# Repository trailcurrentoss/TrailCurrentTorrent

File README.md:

# TrailCurrent Torrent

CAN-controlled 8-channel PWM power distribution module for vehicle lighting and accessory control with OTA firmware update capability and mDNS self-discovery. Up to 3 Torrent modules can operate on the same CAN bus, each with a unique address and CAN IDs. Part of the [TrailCurrent](https://trailcurrent.com) open-source vehicle platform.

## Hardware Overview

- **Microcontroller:** ESP32 (WROOM32)
- **Function:** 8-channel PWM lighting/accessory controller with CAN bus interface
- **Key Features:**
  - 8 independent MOSFET-driven PWM outputs (0-255 brightness)
  - CAN bus communication at 500 kbps
  - Up to 3 modules on the same bus via compile-time `TORRENT_ADDRESS` (0-2)
  - Individual and master on/off/brightness control
  - Animated light sequences (startup, interior, exterior)
  - Over-the-air (OTA) firmware updates via WiFi
  - mDNS self-discovery for automatic registration with Headwaters
  - WiFi credentials provisioned dynamically over CAN bus
  - Hierarchical PCB schematic design (5 sheets)

## Hardware Requirements

### Components

- **Microcontroller:** ESP32 development board
- **CAN Transceiver:** Vehicle CAN bus interface (TX: GPIO 15, RX: GPIO 13)
- **MOSFET Drivers:** 8 channels for PWM output switching
- **DIP Switches:** Configuration switches

### Pin Connections

**PWM Outputs:**

| GPIO | Function |
|------|----------|
| 32 | Output 1 |
| 33 | Output 2 |
| 26 | Output 3 |
| 14 | Output 4 |
| 4 | Output 5 |
| 17 | Output 6 |
| 19 | Output 7 |
| 23 | Output 8 |

### KiCAD Library Dependencies

This project uses the consolidated [TrailCurrentKiCADLibraries](https://github.com/trailcurrentoss/TrailCurrentKiCADLibraries).

**Setup:**

```bash
# Clone the library
git clone git@github.com:trailcurrentoss/TrailCurrentKiCADLibraries.git

# Set environment variables (add to ~/.bashrc or ~/.zshrc)
export TRAILCURRENT_SYMBOL_DIR="/path/to/TrailCurrentKiCADLibraries/symbols"
export TRAILCURRENT_FOOTPRINT_DIR="/path/to/TrailCurrentKiCADLibraries/footprints"
export TRAILCURRENT_3DMODEL_DIR="/path/to/TrailCurrentKiCADLibraries/3d_models"
```

See [KICAD_ENVIRONMENT_SETUP.md](https://github.com/trailcurrentoss/TrailCurrentKiCADLibraries/blob/main/docs/KICAD_ENVIRONMENT_SETUP.md) in the library repository for detailed setup instructions.

## Opening the Project

1. **Set up environment variables** (see Library Dependencies above)
2. **Open KiCAD:**
   ```bash
   kicad EDA/trailcurrent-torrent.kicad_pro
   ```
3. **Verify libraries load** - All symbol and footprint libraries should resolve without errors
4. **View 3D models** - Open PCB and press `Alt+3` to view the 3D visualization

### Schematic Sheets

The design uses a hierarchical schematic with dedicated sheets:
- **Root** - Top-level connections
- **Power** - Power distribution and regulation
- **CAN** - CAN bus transceiver interface
- **MCU** - ESP32 microcontroller and support circuits
- **MOSFETs** - 8-channel MOSFET driver outputs
- **DIP Switch** - Configuration switches

## Firmware

Built with [ESP-IDF](https://docs.espressif.com/projects/esp-idf/en/latest/esp32/) (Espressif IoT Development Framework) targeting the ESP32.

### Prerequisites

Install ESP-IDF v5.x following the [official guide](https://docs.espressif.com/projects/esp-idf/en/latest/esp32/get-started/).

### Build and Flash

```bash
# Set up ESP-IDF environment
source ~/esp/v5.5.2/esp-idf/export.sh

# First time: set chip target
idf.py set-target esp32

# Build firmware (default address 0)
idf.py build

# Build for a specific module address (0-2)
idf.py build -DTORRENT_ADDRESS=1

# Flash and monitor (serial)
idf.py -p /dev/ttyUSB0 flash monitor
```

### Multi-Instance Addressing

Up to 3 Torrent modules can share the same CAN bus. Each module is built with a unique address that determines its CAN IDs:

```bash
idf.py build                      # Address 0 (default)
idf.py build -DTORRENT_ADDRESS=1  # Address 1
idf.py build -DTORRENT_ADDRESS=2  # Address 2
```

Each address produces a firmware binary with unique CAN IDs (see CAN Bus Protocol below). Flash each binary to a different ESP32. At boot, the module logs its address and CAN IDs for verification.

#### Building All Variants

Use `build-all.sh` to build all 3 address variants in a single run:

```bash
./build-all.sh
```

This produces two binaries per address — one for OTA updates, one for the web flasher:

| File | Contents | Used By |
|------|----------|---------|
| `build/torrent_addr{N}.bin` | Application image only | Headwaters OTA (`deploy.sh`, `ota.js`), direct `curl` uploads |
| `build/torrent_addr{N}_merged.bin` | Bootloader + partition table + OTA data + application | Web flasher (full flash at 0x0) |

The two binary types exist because OTA and the web flasher write to different targets. Headwaters OTA sends the binary to the device's `/ota` HTTP endpoint, which calls `esp_ota_write` to write it to a single app partition. That function validates the image as an application — a merged binary starts with the bootloader instead of an app header, so it would fail validation. The web flasher writes the entire flash contents starting at offset 0x0, so it needs all partitions combined into one file.

#### Creating a GitHub Release

After building all variants, attach all 6 binaries (3 app-only + 3 merged) as release assets:

```bash
git tag -a v1.0.0 -m "Firmware release v1.0.0"
git push origin v1.0.0

gh release create v1.0.0 \
  build/torrent_addr0.bin \
  build/torrent_addr1.bin \
  build/torrent_addr2.bin \
  build/torrent_addr0_merged.bin \
  build/torrent_addr1_merged.bin \
  build/torrent_addr2_merged.bin \
  --repo trailcurrentoss/TrailCurrentTorrent \
  --title "v1.0.0" \
  --notes "Firmware release v1.0.0"
```

Both the Headwaters deployment system and the web flasher pull from GitHub releases. The web flasher matches `_merged.bin` files by name for full-flash use. The Headwaters deployment system (`fetch-firmware.sh`) downloads the app-only `torrent_addr{N}.bin` files for OTA delivery.

### OTA Firmware Update

After initial serial flash, firmware can be updated over WiFi:

1. **Provision WiFi credentials** via CAN bus (message ID 0x01)
2. **Trigger OTA mode** via CAN bus (message ID 0x00 with device MAC bytes)
3. **Upload firmware** via HTTP — always use the app-only binary (`torrent_addr{N}.bin`), never the merged binary:
   ```bash
   curl -X POST http://esp32-XXYYZZ.local/ota --data-binary @build/torrent_addr0.bin
   ```

The device enters OTA mode for 3 minutes, starts an HTTP server, and advertises via mDNS. After a successful upload it reboots into the new firmware. Dual OTA partitions provide rollback safety.

### mDNS Self-Discovery

Modules register themselves with the Headwaters controller:

1. **Provision WiFi credentials** via CAN bus (message ID 0x01)
2. **Send discovery trigger** via CAN bus (message ID 0x02, broadcast)
3. Module joins WiFi and advertises a `_trailcurrent._tcp` mDNS service with metadata:
   - `type=torrent` — module type
   - `addr=0` — module address (0-2, from `TORRENT_ADDRESS` build flag)
   - `canid=0x1B` — CAN status message ID (varies by address)
   - `fw=1.0.0` — firmware version
4. Headwaters confirms registration by calling `GET /discovery/confirm`
5. Module tears down WiFi and returns to normal CAN operation

Discovery can be triggered again on subsequent CAN 0x02 broadcasts. A module that is already running a discovery session ignores additional triggers until the current session completes or times out (3 minutes).

### Logging

Firmware uses the ESP-IDF logging system (`ESP_LOGI`, `ESP_LOGW`, `ESP_LOGE`). Log output is available on the serial monitor at 115200 baud.

Log verbosity can be configured at build time via `idf.py menuconfig` under **Component config > Log output**.

**WiFi Credentials:**
- WiFi credentials are provisioned dynamically via CAN bus (Message ID 0x01)
- Credentials are stored in NVS (non-volatile storage) and persist across reboots
- For standalone testing, credentials can be set manually via NVS

### CAN Bus Protocol

CAN IDs are computed as `BASE + TORRENT_ADDRESS`. The table below shows base IDs and per-instance values.

**Receive (Bus → Module):**

| Base ID | Addr 0 | Addr 1 | Addr 2 | Description |
|---------|--------|--------|--------|-------------|
| — | 0x00 | 0x00 | 0x00 | OTA update trigger (3 bytes: last 3 MAC bytes for device targeting) |
| — | 0x01 | 0x01 | 0x01 | WiFi credential provisioning (chunked SSID/password protocol) |
| — | 0x02 | 0x02 | 0x02 | Discovery trigger (broadcast, no payload) |
| — | 0x04 | 0x04 | 0x04 | Version report on boot: `[mac3, mac4, mac5, major, minor, patch]` |
| 0x15 | 0x15 | 0x16 | 0x17 | Set brightness (byte 0 = channel 0-7, byte 1 = PWM value 0-255) |
| 0x18 | 0x18 | 0x19 | 0x1A | Toggle channel on/off (byte 0 = channel 0-7, 8=all off/on, 9=all on) |
| 0x33 | 0x33 | 0x34 | 0x35 | Trigger light sequence (byte 0: 0=interior, 1=exterior) |

**Transmit (Module → Bus):**

| Base ID | Addr 0 | Addr 1 | Addr 2 | Interval | Description |
|---------|--------|--------|--------|----------|-------------|
| 0x1B | 0x1B | 0x1C | 0x1D | 33 ms (30 Hz) | Status report — current PWM values for all 8 channels (8 bytes) |

### WiFi Credential Provisioning Protocol

WiFi credentials are sent over CAN in chunks (max 6 payload bytes per CAN frame):

| Step | data[0] | Payload | Description |
|------|---------|---------|-------------|
| 1 | 0x01 | ssid_len, pass_len, ssid_chunks, pass_chunks | Start message |
| 2 | 0x02 | chunk_index, up to 6 bytes | SSID chunk |
| 3 | 0x03 | chunk_index, up to 6 bytes | Password chunk |
| 4 | 0x04 | XOR checksum | End/commit message |

All messages are sent on CAN ID 0x01. A 5-second timeout resets the state machine if the sequence is interrupted.

## Manufacturing

- **PCB Files:** Ready for fabrication via standard PCB services (JLCPCB, OSH Park, etc.)
- **BOM Generation:** Export BOM from KiCAD schematic (Tools > Generate BOM)
- **JLCPCB Assembly:** See [BOM_ASSEMBLY_WORKFLOW.md](https://github.com/trailcurrentoss/TrailCurrentKiCADLibraries/blob/main/tools/BOM_ASSEMBLY_WORKFLOW.md) for detailed assembly workflow

## Project Structure

```
├── EDA/                          # KiCAD hardware design files
│   ├── trailcurrent-torrent.kicad_pro
│   ├── trailcurrent-torrent.kicad_sch  # Root schematic
│   ├── can.kicad_sch             # CAN subsystem
│   ├── mcu.kicad_sch             # MCU subsystem
│   ├── power.kicad_sch           # Power subsystem
│   ├── mosfets.kicad_sch         # 8-channel MOSFET drivers
│   ├── dip_switch.kicad_sch      # Configuration switches
│   └── trailcurrent-torrent.kicad_pcb  # PCB layout
├── CAD/                          # FreeCAD case design and 3D models
│   ├── trailcurrent-torrent-case.FCStd
│   └── TrailCurrentTorrent.3mf
├── main/                         # ESP-IDF firmware source
│   ├── main.c                    # App entry, LEDC PWM, TWAI CAN task, light sequences
│   ├── ota.h / ota.c             # OTA updates, WiFi management, credential provisioning
│   ├── discovery.h / discovery.c # mDNS self-discovery and Headwaters registration
│   ├── CMakeLists.txt            # Component build config
│   └── idf_component.yml         # ESP-IDF component dependencies
├── partitions.csv                # ESP32 flash partition layout (dual OTA)
├── sdkconfig.defaults            # ESP-IDF build defaults
├── build-all.sh                  # Build all 3 address variants (addr 0-2)
└── CMakeLists.txt                # Root ESP-IDF project config
```

## License

MIT License - See LICENSE file for details.

This is open source hardware. You are free to use, modify, and distribute these designs under the terms of the MIT license.

## Contributing

Improvements and contributions are welcome! Please submit issues or pull requests.

## Support

For questions about:
- **KiCAD setup:** See [KICAD_ENVIRONMENT_SETUP.md](https://github.com/trailcurrentoss/TrailCurrentKiCADLibraries/blob/main/docs/KICAD_ENVIRONMENT_SETUP.md)
- **Assembly workflow:** See [BOM_ASSEMBLY_WORKFLOW.md](https://github.com/trailcurrentoss/TrailCurrentKiCADLibraries/blob/main/tools/BOM_ASSEMBLY_WORKFLOW.md)

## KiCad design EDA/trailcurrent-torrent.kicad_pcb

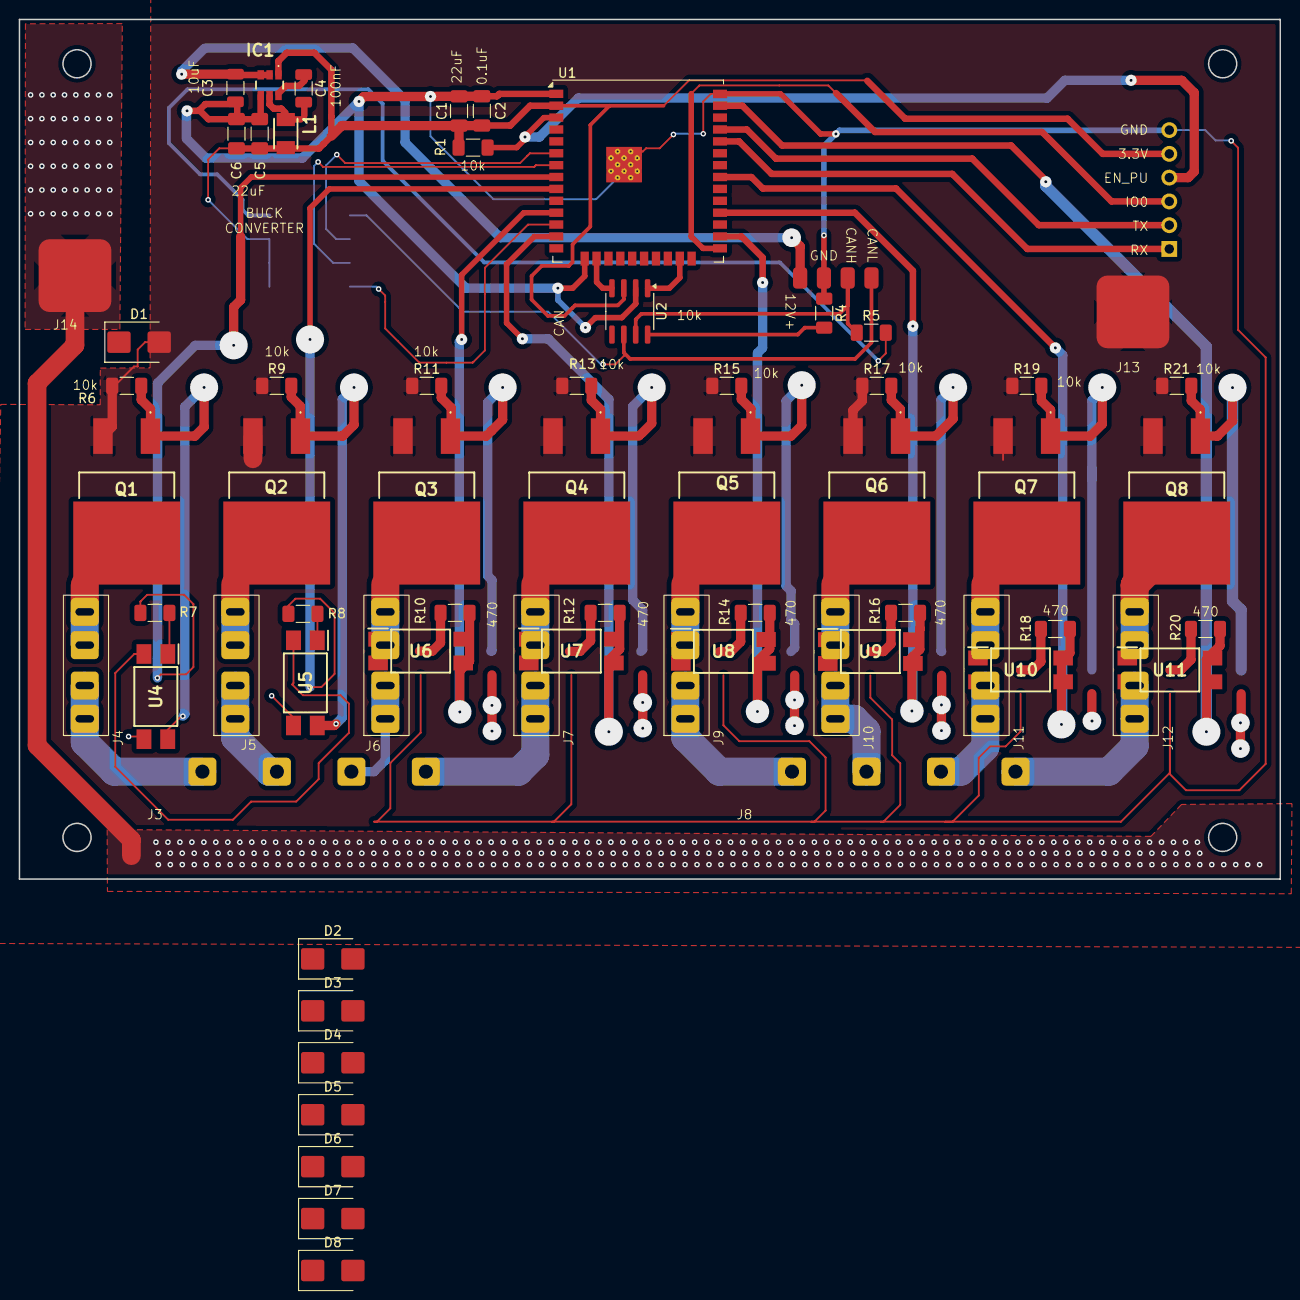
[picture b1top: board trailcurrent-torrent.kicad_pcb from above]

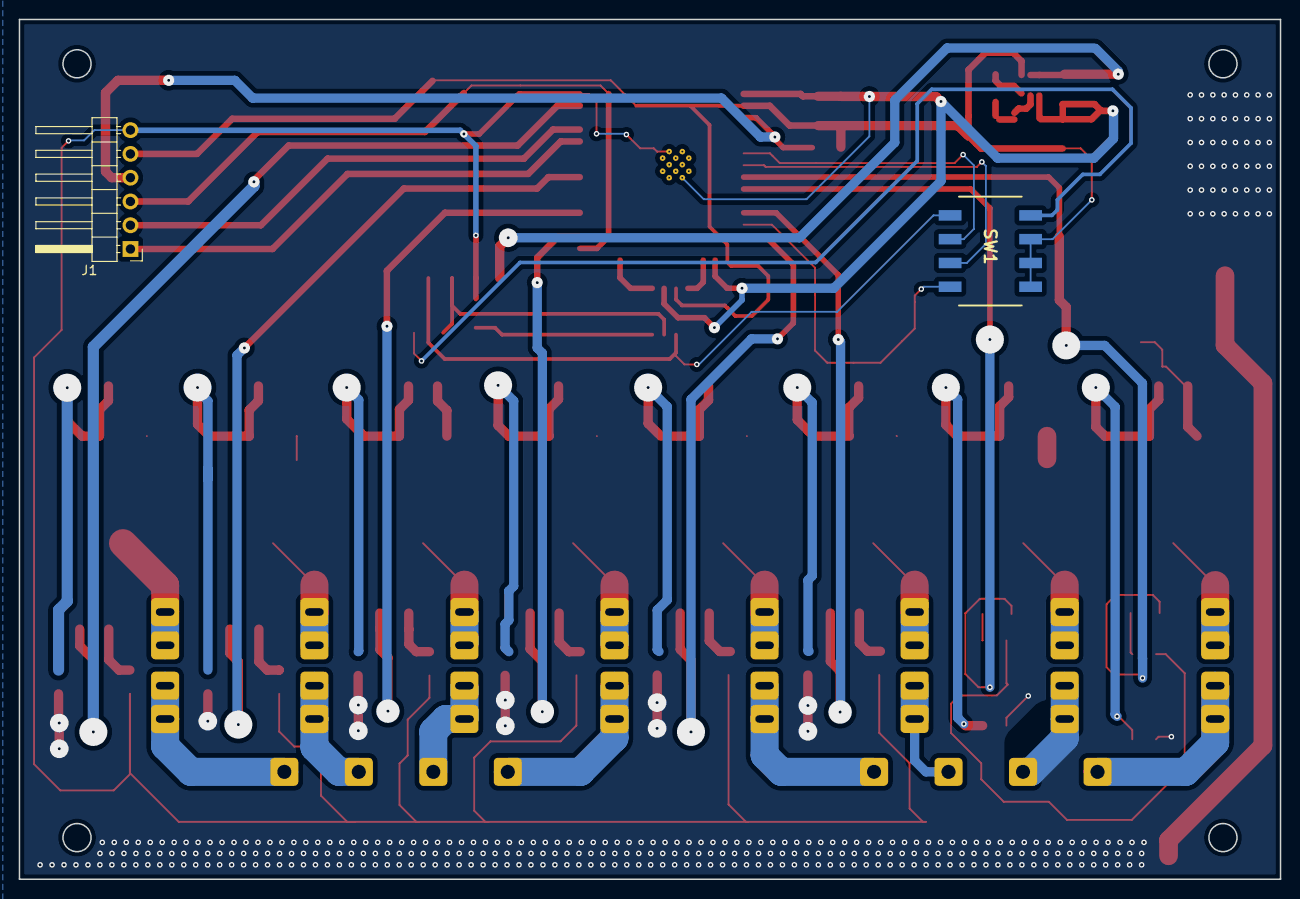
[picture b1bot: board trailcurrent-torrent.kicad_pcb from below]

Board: 2 copper layers, 134.7 x 91.9 mm, 68 parts (2 on the bottom side), 60 nets.

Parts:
C1, C5, C6: 22uF; C_1206_3216Metric_Pad1.33x1.80mm_HandSolder
C2: 0.1uF; C_1206_3216Metric_Pad1.33x1.80mm_HandSolder
C3: 10uF; C_1206_3216Metric
C4: 100nF; C_1206_3216Metric
D1, D2, D3, D4, D5, D6, D7, D8: SS54; D_SMB
IC1: AP63203WU-7; AP63203WU7
J1: Conn_01x06; PinHeader_1x06_P2.54mm_Horizontal
J2: Conn_01x04; CAN_PLUS_POWER
J3, J8: Conn_01x04; Screw_Terminal_1x04
J4, J5, J6, J7, J9, J10, J11, J12: Conn_01x04; Automotive_Fuse_Holder
J13, J14: Conn_01x01; TestPoint_7.77mmX7.77mm
L1: NLV32T-3R9J-EF (3.9uH); NLV32T-3R9J-EF
Q1, Q2, Q3, Q4, Q5, Q6, Q7, Q8: IRF4905STRLPBF
R1, R4, R6, R9, R11, R13, R15, R17, R19, R21: 10k; R_1206_3216Metric_Pad1.30x1.75mm_HandSolder
R5: 120; R_1206_3216Metric_Pad1.30x1.75mm_HandSolder
R7, R8, R10, R12, R14, R16, R18, R20: 470; R_1206_3216Metric_Pad1.30x1.75mm_HandSolder
SW1: SW_DIP_x04; SW_DIP_219-4LPST
U1: ESP32-WROOM-32; ESP32-WROOM-32U
U2: SN65HVD230; SOIC-8_3.9x4.9mm_P1.27mm
U4, U5, U6, U7, U8, U9, U10, U11: PC817; PC817X3CSP9F

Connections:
12V_OUT01: D1.1 (K), J4.3, J4.4, Q1.2 (D)
12V_OUT02: D2.1 (K), J5.3, J5.4, Q2.2 (D)
12V_OUT03: D3.1 (K), J6.3, J6.4, Q3.2 (D)
12V_OUT04: D4.1 (K), J7.3, J7.4, Q4.2 (D)
12V_OUT05: D5.1 (K), J9.3, J9.4, Q5.2 (D)
12V_OUT06: D6.1 (K), J10.3, J10.4, Q6.2 (D)
12V_OUT07: D7.1 (K), J11.3, J11.4, Q7.2 (D)
12V_OUT08: D8.1 (K), J12.3, J12.4, Q8.2 (D)
+3.3V: C1.1, C2.1, C5.1, C6.1, IC1.1 (FB), J1.5, L1.2, R1.1, SW1.5, SW1.6, SW1.7, U1.2 (VDD), U2.3 (VCC)
+12V: C3.1, IC1.2 (EN), IC1.3 (VIN), J2.1
+15V: D1.2 (A), D2.2 (A), D3.2 (A), D4.2 (A), D5.2 (A), D6.2 (A), D7.2 (A), D8.2 (A), J13.1, Q1.3 (S), Q2.3 (S), Q3.3 (S), Q4.3 (S), Q5.3 (S), Q6.3 (S), Q7.3 (S), Q8.3 (S), R6.1, R9.1, R11.1, R13.1, R15.1, R17.1, R19.1, R21.1
CANH: J2.3, R5.1, U2.7 (CANH)
CANL: J2.4, SW1.1, U2.6 (CANL)
CAN_RX: U1.16 (IO13), U2.4 (R)
CAN_TERM_CLOSED: R5.2, SW1.8
CAN_TX: U1.23 (IO15), U2.1 (D)
DEVICE01: R7.1, U1.8 (IO32)
DEVICE02: R8.1, U1.9 (IO33)
DEVICE03: R10.1, U1.11 (IO26)
DEVICE04: R12.1, U1.13 (IO14)
DEVICE05: R14.1, U1.26 (IO4)
DEVICE06: R16.1, U1.28 (IO17)
DEVICE07: R18.1, U1.31 (IO19)
DEVICE08: R20.1, U1.37 (IO23)
DEVICE_SELECTION01: SW1.2, U1.6 (IO34)
DEVICE_SELECTION02: SW1.3, U1.7 (IO35)
DEVICE_SELECTION03: SW1.4, U1.12 (IO27)
EN: J1.4, R1.2, U1.3 (EN)
ESP32_RX: J1.1, U1.34 (RXD0/IO3)
ESP32_TX: J1.2, U1.35 (TXD0/IO1)
GND: C1.2, C2.2, C3.2, C5.2, C6.2, IC1.4 (GND), J1.6, J2.2, R4.1, U1.1 (GND), U1.15 (GND), U1.38 (GND), U1.39 (GND), U2.2 (GND), U4.2, U5.2, U6.2, U7.2, U8.2, U9.2, U10.2, U11.2
GND1: J14.1, U4.3, U5.3, U6.3, U7.3, U8.3, U9.3, U10.3, U11.3
IO0: J1.3, U1.25 (IO0)
LOAD01: J3.1, J4.1, J4.2
LOAD02: J3.2, J5.1, J5.2
LOAD03: J3.3, J6.1, J6.2
LOAD04: J3.4, J7.1, J7.2
LOAD05: J8.1, J9.1, J9.2
LOAD06: J8.2, J10.1, J10.2
LOAD07: J8.3, J11.1, J11.2
LOAD08: J8.4, J12.1, J12.2
unnamed: C4.1, IC1.6 (BST)
unnamed: C4.2, IC1.5 (SW), L1.1
unnamed: Q1.1 (G), R6.2, U4.4
unnamed: Q2.1 (G), R9.2, U5.4
unnamed: Q3.1 (G), R11.2, U6.4
unnamed: Q4.1 (G), R13.2, U7.4
unnamed: Q5.1 (G), R15.2, U8.4
unnamed: Q6.1 (G), R17.2, U9.4
unnamed: Q7.1 (G), R19.2, U10.4
unnamed: Q8.1 (G), R21.2, U11.4
unnamed: R7.2, U4.1
unnamed: R8.2, U5.1
unnamed: R10.2, U6.1
unnamed: R12.2, U7.1
unnamed: R14.2, U8.1
unnamed: R16.2, U9.1
unnamed: R18.2, U10.1
unnamed: R20.2, U11.1
unnamed: R4.2, U2.8 (Rs)

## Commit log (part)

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2026-03-08 Rename
2026-03-15 Updated to use fixed library
2026-03-19 Adding assembled image to readme
2026-03-26 Moving to ESP-IDF
2026-03-26 More robust CAN handling allowing recovery and nodes to enter/leave the network
2026-03-27 Discovery verified working for Torrent
2026-03-28 Fixed bug where discovery would disrupt CAN messaging
2026-03-28 Torrent now allowed multiple modules
2026-03-28 Aligned OTA and discovery
2026-03-28 Fixing issue with CAN Bus stops responding when discovery happens
2026-03-29 Changes to provide version on OTA
2026-04-09 Added build script for all variants with different addresses
2026-04-09 Fixed merged binaries for releasese
2026-04-10 Upadated build script to produce files needed for both web flash and OTA.
2026-04-15 Aligning CAN Bus implementation with Switchback for more robust handling of varios edge cases.
2026-04-15 Working on pattern that will be repeated for all CAN Bus scenarios
2026-04-15 Testing another release
2026-04-15 Testing versioning
2026-04-15 Moved to use the new can library
